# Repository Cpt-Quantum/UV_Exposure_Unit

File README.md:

# UV_Exposure_Unit
A directory for my UV exposure unit with code for a PIC18F45K50, and schematics.

Due to the nature of the electronic arrangement for this project a picture will be provided of the finished project to show how it is all assembled. The boards are all quite small and were designed to be modular, none of which are particularly complicated individually. The reason I went for an active control system for this project was so that it was self timing and then would shut off, so that it does not need to be managed, as the circuit board being exposed can be quite sensitive as to how much UV exposure it recieves.

A quick note: The PIC had to be changed midway through development due to one of the ports on my PIC16F877A being damaged, this made setting the individual bits on port B clear the states of the other pins in port B. This made my LCD library non-functional since it sets the individual bits. I have now changed the project to use the PIC18F45K50, I will be updating the schematics accordingly when I get round to finishing them.

The credit for the debouncing algorithm goes to Jack Ganssle. I do recommend reading his document on button debouncing (http://www.ganssle.com/debouncing.htm) as it goes into a lot of detail behind button bounce. The algorithm is particularly well designed to be called on an interrupt to minimise load on the CPU caused by traditional methods which use __delay(...). I have not implemented it this way for this project as the load on the CPU is relatively low.

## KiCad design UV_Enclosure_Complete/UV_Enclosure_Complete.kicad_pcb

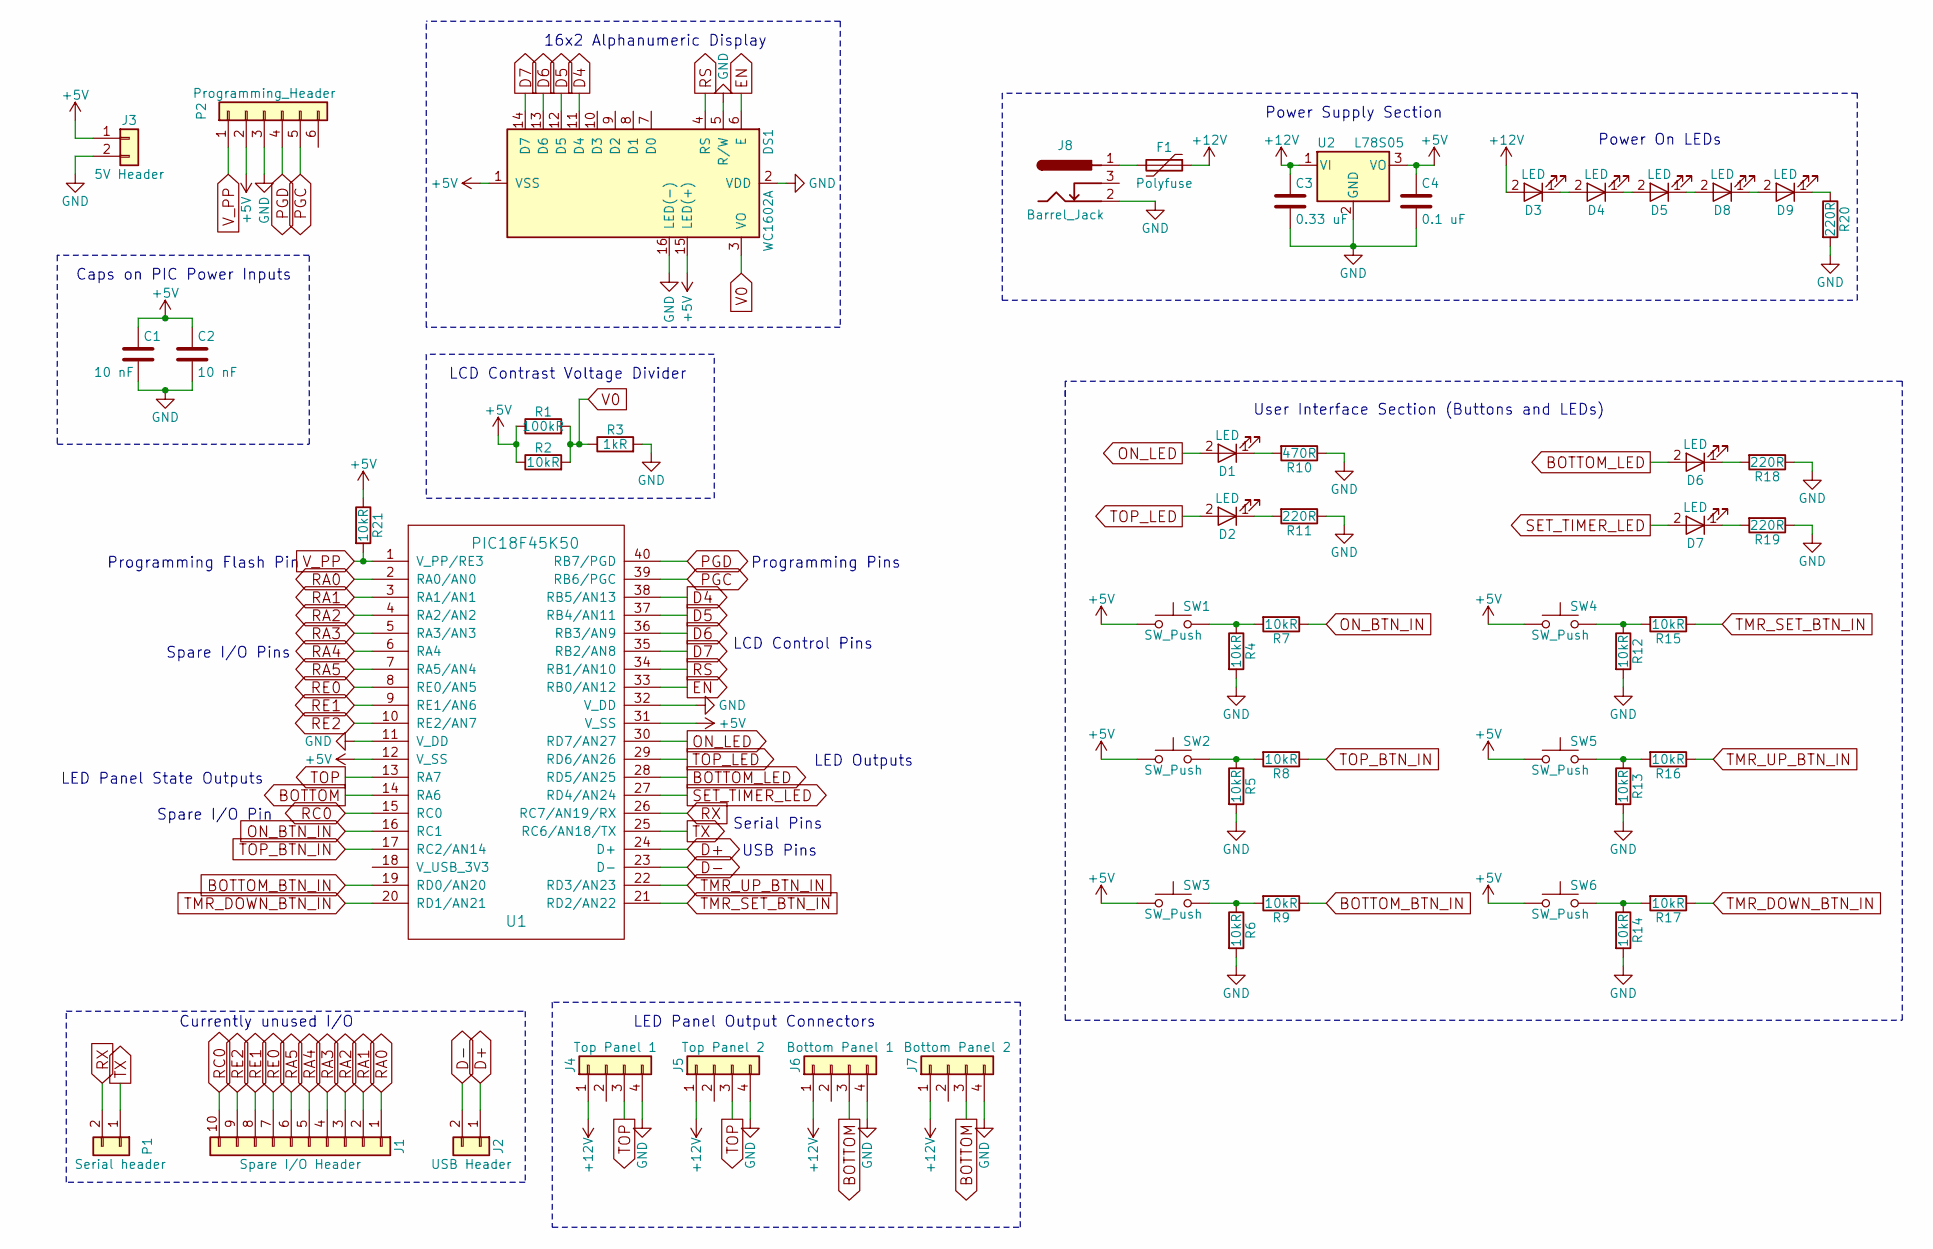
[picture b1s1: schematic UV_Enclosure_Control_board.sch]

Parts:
C1, C2: 10 nF; C_Disc_D3.0mm_W2.0mm_P2.50mm
C3: 0.33 uF; C_Rect_L9.0mm_W4.9mm_P7.50mm_MKT
C4: 0.1 uF; C_Rect_L9.0mm_W3.2mm_P7.50mm_MKT
D1, D2, D3, D4, D5, D6, D7, D8, D9: LED; LED_D5.0mm
DS1: WC1602A
F1: Polyfuse; Polyfuse-2A-Square-Horizontal
J1: Spare I/O Header; Pin_Header_Straight_1x10_Pitch2.54mm
J2: USB Header; Pin_Header_Straight_1x02_Pitch2.54mm
J3: 5V Header; Pin_Header_Straight_1x02_Pitch2.54mm
J4: Top Panel 1; Pin_Header_Straight_1x04_Pitch2.54mm
J5: Top Panel 2; Pin_Header_Straight_1x04_Pitch2.54mm
J6: Bottom Panel 1; Pin_Header_Straight_1x04_Pitch2.54mm
J7: Bottom Panel 2; Pin_Header_Straight_1x04_Pitch2.54mm
J8: Barrel_Jack; BARREL_JACK
P1: Serial header; Pin_Header_Straight_1x02_Pitch2.54mm
P2: Programming_Header; Pin_Header_Straight_1x06_Pitch2.54mm
R1: 100kR; R_Axial_DIN0309_L9.0mm_D3.2mm_P12.70mm_Horizontal
R2, R4, R5, R6, R7, R8, R9, R12, R13, R14, R15, R16, R17, R21: 10kR; R_Axial_DIN0309_L9.0mm_D3.2mm_P12.70mm_Horizontal
R3: 1kR; R_Axial_DIN0309_L9.0mm_D3.2mm_P12.70mm_Horizontal
R10: 470R; R_Axial_DIN0309_L9.0mm_D3.2mm_P12.70mm_Horizontal
R11, R18, R19, R20: 220R; R_Axial_DIN0309_L9.0mm_D3.2mm_P12.70mm_Horizontal
SW1, SW2, SW3, SW4, SW5, SW6: SW_Push; SW_Tactile_Straight_KSA0Axx1LFTR
U1: PIC18F45K50; DIP-40_0
U2: L78S05; TO-220-3_Horizontal

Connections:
+5V: C1.1, C2.1, C4.1, DS1.1 (VSS), DS1.15 (LED(+)), J3.1, P2.2, R1.1, R2.1, R21.1, SW1.1, SW2.1, SW3.1, SW4.1, SW5.1, SW6.1, U1.12 (V_SS), U1.31 (V_SS), U2.3 (VO)
+12V: C3.1, D3.2 (A), F1.1, J4.1, J5.1, J6.1, J7.1, U2.1 (VI)
BOTTOM: J6.3, J7.3, U1.14 (RA6)
BOTTOM_BTN_IN: R9.1, U1.19 (RD0/AN20)
BOTTOM_LED: D6.2 (A), U1.28 (RD5/AN25)
D4: DS1.11 (D4), U1.38 (RB5/AN13)
D5: DS1.12 (D5), U1.37 (RB4/AN11)
D6: DS1.13 (D6), U1.36 (RB3/AN9)
D7: DS1.14 (D7), U1.35 (RB2/AN8)
D+: J2.1, U1.24 (D+)
D-: J2.2, U1.23 (D-)
EN: DS1.6 (E), U1.33 (RB0/AN12)
GND: C1.2, C2.2, C3.2, C4.2, DS1.2 (VDD), DS1.5 (R/W), DS1.16 (LED(-)), J3.2, J4.4, J5.4, J6.4, J7.4, J8.2, P2.3, R3.2, R4.2, R5.2, R6.2, R10.1, R11.1, R12.2, R13.2, R14.2, R18.1, R19.1, R20.2, U1.11 (V_DD), U1.32 (V_DD), U2.2 (GND)
unnamed: D1.1 (K), R10.2
unnamed: D2.1 (K), R11.2
unnamed: D3.1 (K), D4.2 (A)
unnamed: D4.1 (K), D5.2 (A)
unnamed: D5.1 (K), D8.2 (A)
unnamed: D6.1 (K), R18.2
unnamed: D7.1 (K), R19.2
unnamed: D8.1 (K), D9.2 (A)
unnamed: D9.1 (K), R20.1
unnamed: F1.2, J8.1
unnamed: R4.1, R7.2, SW1.2
unnamed: R5.1, R8.2, SW2.2
unnamed: R6.1, R9.2, SW3.2
unnamed: R12.1, R15.2, SW4.2
unnamed: R13.1, R16.2, SW5.2
unnamed: R14.1, R17.2, SW6.2
ON_BTN_IN: R7.1, U1.16 (RC1)
ON_LED: D1.2 (A), U1.30 (RD7/AN27)
PGC: P2.5, U1.39 (RB6/PGC)
PGD: P2.4, U1.40 (RB7/PGD)
RA0: J1.1, U1.2 (RA0/AN0)
RA1: J1.2, U1.3 (RA1/AN1)
RA2: J1.3, U1.4 (RA2/AN2)
RA3: J1.4, U1.5 (RA3/AN3)
RA4: J1.5, U1.6 (RA4)
RA5: J1.6, U1.7 (RA5/AN4)
RC0: J1.10, U1.15 (RC0)
RE0: J1.7, U1.8 (RE0/AN5)
RE1: J1.8, U1.9 (RE1/AN6)
RE2: J1.9, U1.10 (RE2/AN7)
RS: DS1.4 (RS), U1.34 (RB1/AN10)
RX: P1.2, U1.26 (RC7/AN19/RX)
SET_TIMER_LED: D7.2 (A), U1.27 (RD4/AN24)
TMR_DOWN_BTN_IN: R17.1, U1.20 (RD1/AN21)
TMR_SET_BTN_IN: R15.1, U1.21 (RD2/AN22)
TMR_UP_BTN_IN: R16.1, U1.22 (RD3/AN23)
TOP: J4.3, J5.3, U1.13 (RA7)
TOP_BTN_IN: R8.1, U1.17 (RC2/AN14)
TOP_LED: D2.2 (A), U1.29 (RD6/AN26)
TX: P1.1, U1.25 (RC6/AN18/TX)
V0: DS1.3 (VO), R1.2, R2.2, R3.1
V_PP: P2.1, R21.2, U1.1 (V_PP/RE3)

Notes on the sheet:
Programming Pins
LCD Control Pins
LED Outputs
Serial Pins
USB Pins
Spare I/O Pins
Programming Flash Pin
LED Panel State Outputs
Spare I/O Pin
Caps on PIC Power Inputs
Currently unused I/O
LED Panel Output Connectors
Power On LEDs
Power Supply Section
User Interface Section (Buttons and LEDs)
LCD Contrast Voltage Divider
16x2 Alphanumeric Display

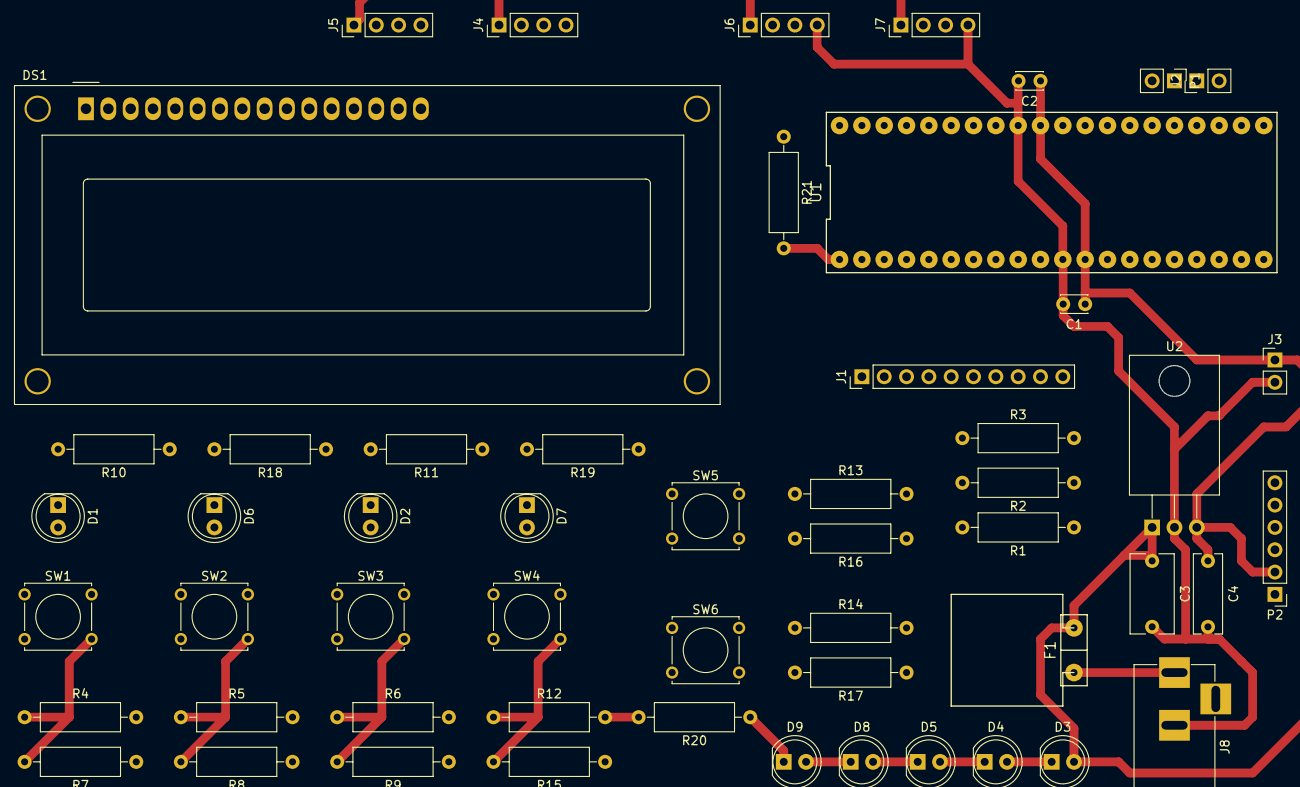
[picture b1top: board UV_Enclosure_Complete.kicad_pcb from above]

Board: 2 copper layers, 54 parts (0 on the bottom side), 55 nets.

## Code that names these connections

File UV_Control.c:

/*
 * File:   UV_Control.c
 * Author: Connor
 *
 * Created on April 14, 2017, 3:02 PM
 */


// PIC16F886 Configuration Bit Settings

// 'C' source line config statements

#include <xc.h>
#include "LCD.h"

// #pragma config statements should precede project file includes.
// Use project enums instead of #define for ON and OFF.

// CONFIG1
#pragma config FOSC = INTRC_NOCLKOUT// Oscillator Selection bits (INTOSCIO oscillator: I/O function on RA6/OSC2/CLKOUT pin, I/O function on RA7/OSC1/CLKIN)
#pragma config WDTE = OFF       // Watchdog Timer Enable bit (WDT disabled and can be enabled by SWDTEN bit of the WDTCON register)
#pragma config PWRTE = OFF      // Power-up Timer Enable bit (PWRT disabled)
#pragma config MCLRE = ON       // RE3/MCLR pin function select bit (RE3/MCLR pin function is MCLR)
#pragma config CP = OFF         // Code Protection bit (Program memory code protection is disabled)
#pragma config CPD = OFF        // Data Code Protection bit (Data memory code protection is disabled)
#pragma config BOREN = ON       // Brown Out Reset Selection bits (BOR enabled)
#pragma config IESO = ON        // Internal External Switchover bit (Internal/External Switchover mode is enabled)
#pragma config FCMEN = ON       // Fail-Safe Clock Monitor Enabled bit (Fail-Safe Clock Monitor is enabled)
#pragma config LVP = OFF        // Low Voltage Programming Enable bit (RB3 pin has digital I/O, HV on MCLR must be used for programming)

// CONFIG2
#pragma config BOR4V = BOR40V   // Brown-out Reset Selection bit (Brown-out Reset set to 4.0V)
#pragma config WRT = OFF        // Flash Program Memory Self Write Enable bits (Write protection off)

#include <stdint.h>

//Define oscillator frequency for delay function use
#define _XTAL_FREQ 4000000

//Define the pins for the buttons
#define ON_BTN_IN           RA5         
#define TOP_BTN_IN          RA4
#define BOTTOM_BTN_IN       RA3
#define TMR_DOWN_BTN_IN     RA2
#define TMR_UP_BTN_IN       RA1
#define TMR_SET_BTN_IN      RA0

//Define the pins for the status LEDs
#define ON_LED              RC3
#define TOP_LED             RC2
#define BOTTOM_LED          RC1
#define SET_TIMER_LED       RC0

//Define the pins for the MOSFET switches
#define TOP_STATE           RA7
#define BOTTOM_STATE        RA6

//Variable to store the on time in seconds - default of 30 seconds
uint16_t on_time = 30;

//Prototype function declarations
//Debounce and latching function for each button
void debounce1();
void debounce2();
void debounce3();
void debounce4();
void debounce5();
void debounce6();

void main(void) {
    //Turn off the comparators and analogue inputs
    ANSEL = 0x00;
    CM1CON0 = 0x07;
    CM2CON0 = 0x07;
   
    //Initialise the ports as needed
    TRISC = 0xF0;   //Set RC0-3 as outputs and 4-7 as inputs
    TRISA = 0x3F;   //Set RA0-5 as inputs and 6&7 as outputs
    TRISB = 0xC0;   //Set RB0-5 as outputs and 6&7 as inputs
  
    //Initialise LCD
//    LCD_Initialise(1,0,1,1);
    
    //Move to start position
//    LCD_Cursor_Position(1,1);
    
//    LCD_Write_Char("H");
    
    RB0=1;
    RB1=1;
    RB2=1;
    RB3=1;
    RB4=1;
    RB5=1;
    
    //Start while loop to keep the program looping forever    
    while(1){
    
    //Initialise the pins set as outputs to safe values
    ON_LED = 0;
    TOP_LED = 0;
    BOTTOM_LED = 0;
    SET_TIMER_LED = 0;
    TOP_STATE = 0;
    BOTTOM_STATE = 0;


    
    //Button read state:
    //This is the initial state, the PIC waits for the user to push the ON_BTN
    // to put the PIC into the on state. This is also the state to set the timer
    // and which LED panels (top or bottom) to turn on.
    while (ON_LED == 0) {
        //Read the buttons and set the states accordingly
        debounce1();
        debounce2();
        debounce3();
        debounce6();
        
        //If the timer set button has been activated, read the button states for
        // the up/down user inputs and wait until user presses the timer set 
        //button again.
        while (SET_TIMER_LED == 1){
            //Set timer with buttons
            debounce4();
            debounce5();
            debounce6();
        }
        __delay_ms(1);
    }
    
    
    //On state:
    //This is the state where the PIC switches on the LED panels and counts up
    // to the set timer amount and then switches off the panels. It then goes
    //back in to the button read state. The system can also exit this state if
    // the user presses the on/off button
    
    //Switch on the MOSFETs according to the user set state (held in the LED 
    //states)
    TOP_STATE=TOP_LED;
    BOTTOM_STATE=BOTTOM_LED;
    
    //Begin counter
    for(int i=0; (i<(1000*on_time)); i++){
        debounce1();
        if (ON_LED == 0) break;
        __delay_ms(1);
    }
    
    }//End program while loop
}

//Debounce functions. Credit goes to Jack Ganssle for the original algorithm
//This function is called on a regular interrupt inside the latching function

void debounce1(){
    static uint16_t State1;              //Current debounce status
    State1 = (State1<<1 | !ON_BTN_IN | 0xE000);
    if(State1 == 0xF000){
        ON_LED=!ON_LED;
        State1 = 0x0000;
    }
}

void debounce2(){
    static uint16_t State2;              //Current debounce status
    State2 = (State2<<1 | !TOP_BTN_IN | 0xE000);
    if(State2 == 0xF000){
        TOP_LED=!TOP_LED;
        State2 = 0x0000;
    }
}

void debounce3(){
    static uint16_t State3;              //Current debounce status
    State3 = (State3<<1 | !BOTTOM_BTN_IN | 0xE000);
    if(State3 == 0xF000){
        BOTTOM_LED=!BOTTOM_LED;
        State3 = 0x0000;
    }
}

void debounce4(){
    static uint16_t State4;              //Current debounce status
    State4 = (State4<<1 | !TMR_DOWN_BTN_IN | 0xE000);
    if(State4 == 0xF000){
        on_time = on_time - 1;
        State4 = 0x0000;
    }
}

void debounce5(){
    static uint16_t State5;              //Current debounce status
    State5 = (State5<<1 | !TMR_UP_BTN_IN | 0xE000);
    if(State5 == 0xF000){
        TOP_LED=!TOP_LED;
        State5 = 0x0000;
    }
}

void debounce6(){
    static uint16_t State6;              //Current debounce status
    State6 = (State6<<1 | !TMR_SET_BTN_IN | 0xE000);
    if(State6 == 0xF000){
        SET_TIMER_LED=!SET_TIMER_LED;
        State6 = 0x0000;
    }
}

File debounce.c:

/*
 * File:   debounce.c
 * Author: Connor
 *
 * Created on August 12, 2017, 6:03 PM
 * 
 * This file handles the user inputs and states set by the user
 */


#include <xc.h>
#include "debounce.h"
#include <stdint.h>

//Define the pins for the buttons
#define ON_BTN_IN           PORTCbits.RC1    
#define TOP_BTN_IN          PORTCbits.RC2
#define BOTTOM_BTN_IN       PORTDbits.RD0
#define TMR_DOWN_BTN_IN     PORTDbits.RD1
#define TMR_UP_BTN_IN       PORTDbits.RD3
#define TMR_SET_BTN_IN      PORTDbits.RD2

//Define the pins for the status LEDs
#define ON_LED              LATDbits.LATD7
#define TOP_LED             LATDbits.LATD6
#define BOTTOM_LED          LATDbits.LATD5
#define SET_TIMER_LED       LATDbits.LATD4


//Variable to store the on time in seconds - default of 30 seconds
unsigned long on_time = 30;

//Debounce functions. Credit goes to Jack Ganssle for the original algorithm
//This function is called on a regular interrupt inside the latching function

void debounce_ON_BTN(){
    static uint16_t State1;              //Current debounce status
    State1 = (State1<<1 | !ON_BTN_IN | 0xE000);
    if(State1 == 0xF000){
        ON_LED=!ON_LED;
        State1 = 0x0000;
    }
}

void debounce_TOP_BTN(){
    static uint16_t State2;              //Current debounce status
    State2 = (State2<<1 | !TOP_BTN_IN | 0xE000);
    if(State2 == 0xF000){
        TOP_LED=!TOP_LED;
        State2 = 0x0000;
    }
}

void debounce_BOTTOM_BTN(){
    static uint16_t State3;              //Current debounce status
    State3 = (State3<<1 | !BOTTOM_BTN_IN | 0xE000);
    if(State3 == 0xF000){
        BOTTOM_LED=!BOTTOM_LED;
        State3 = 0x0000;
    }
}

void debounce_TMR_DOWN_BTN(){
    static uint16_t State4;              //Current debounce status
    State4 = (State4<<1 | !TMR_DOWN_BTN_IN | 0xE000);
    if(State4 == 0xF000){
        on_time = on_time - 10;
        State4 = 0x0000;
    }
}

void debounce_TMR_UP_BTN(){
    static uint16_t State5;              //Current debounce status
    State5 = (State5<<1 | !TMR_UP_BTN_IN | 0xE000);
    if(State5 == 0xF000){
        on_time = on_time + 10;
        State5 = 0x0000;
    }
}

void debounce_TMR_SET_BTN(){
    static uint16_t State6;              //Current debounce status
    State6 = (State6<<1 | !TMR_SET_BTN_IN | 0xE000);
    if(State6 == 0xF000){
        SET_TIMER_LED=!SET_TIMER_LED;
        State6 = 0x0000;
    }
}

//Initialisation function to set all outputs to zero
void debounce_initialise(){
    //Initialise relevant ports
    TRISD = 0x0F;
    TRISC = 0x0F;
    
    //Initialise the pins set as outputs to safe values
    ON_LED = 0;
    TOP_LED = 0;
    BOTTOM_LED = 0;
    SET_TIMER_LED = 0;
}

//State handling functions
uint8_t ON_State(){return ON_LED;}
uint8_t TMR_SET_State(){return SET_TIMER_LED;}
uint8_t TOP_State(){return TOP_LED;}
uint8_t BOTTOM_State(){return BOTTOM_LED;}

//Function to reset all states
void Reset_States(){
    ON_LED = SET_TIMER_LED = TOP_LED = BOTTOM_LED = 0;
}

//Function to return the set on_time
unsigned long On_Time(){return on_time;}

//Function to set the on time
void Set_On_Time(unsigned long set_on_time){on_time = set_on_time;}

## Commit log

2017-08-21 Changed header files
    Changed header files to work with the new PIC. Also separated the button inputs and LED output handling into its own header.
2017-08-21 New main
    Changed main c file to be main.c, updated code to probe and test the LCD and debounce headers.
2017-08-22 Added for loop to initialise state
    Added a for loop to the initialise state to reduce the effect of the __delay_ms waits present in the LCD code. The for loop basically calls 100 debounce cycles before updating the display, leading to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
2017-08-23 Changed from UV_Control.c to main.C
    Changed file name as well as adding a for loop to the initialisation
    state to reduce the effect of the __delay_ms waits in the LCD function
    calls.
2017-08-30 Added general functions header
    Added a general functions header to handle conversion between the time stored in seconds and the display the time in minutes/seconds on the LCD. These functions have also been implemented in main.c.
    As a side note, I also added a set function for the on_time variable to allow for a global variable to store the user set on time between runs of the software (not saved between power cycles though).
2017-08-30 Revert "Revert "Added general functions header""
    This reverts commit 4643dd338e4f4dd2f26b40bc4247b835f92d1ce2, reversing
    changes made to 7d9e59b4d017d6996570e25517b1465593b57b1f.
2017-08-30 Updated schematic for control board
    Updated the schematic for the new control board with new PIC (PIC18F45K50). This was changed due to the original PIC having non-functioning pins on PORTB.
2017-08-30 Create LICENSE
2017-11-04 Change time variables from int to unsigned long
    The time variables have been switched from uint16_t to unsigned long which allows a much larger maximum time.
2017-11-11 Created the complete control board schematic. This superceds the other schematics.
2017-11-11 Re-organised the repositories relating to the schematic folders, this is due to the consolidation of all schematic information into one schematic sheet.
2017-11-11 Changed LCD header to an LCD component.
2017-11-12 Added 5V header just in case any future additions require it.
2017-11-13 Started board layout: Finished initial component layout.
2017-11-13 Added pull up resistor on V_PP and started routing traces.
